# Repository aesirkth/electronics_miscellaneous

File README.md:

# electronics_miscellaneous
Various smaller electronics projects

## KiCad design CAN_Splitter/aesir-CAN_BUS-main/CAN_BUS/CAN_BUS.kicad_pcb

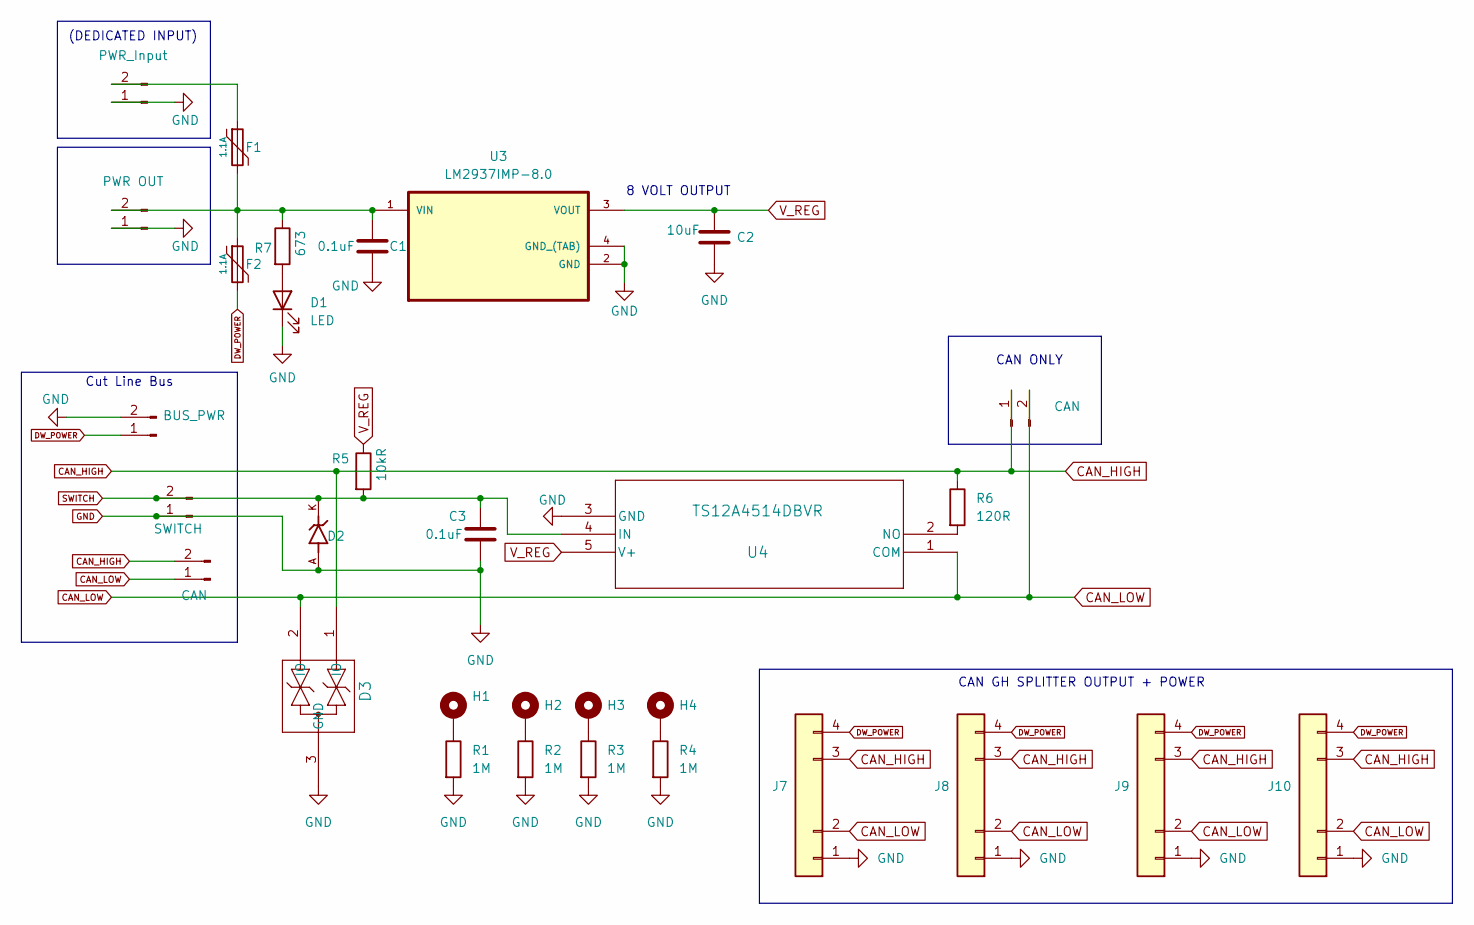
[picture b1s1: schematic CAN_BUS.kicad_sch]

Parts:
C1, C3: 0.1uF; C_0805_2012Metric_Pad1.18x1.45mm_HandSolder
C2: 10uF; C_0805_2012Metric_Pad1.18x1.45mm_HandSolder
D1: LED; LED_1206_3216Metric_Pad1.42x1.75mm_HandSolder
D2: UCLAMP1071P.TNT; DIO_UCLAMP1071P.TNT; PARTREV 8.1
D3: ESD2CAN36DBZRQ1; SOT-23-3_DBZ_TEX
F1, F2: 1.1A; Fuse_1812_4532Metric_Pad1.30x3.40mm_HandSolder
H1, H2, H3, H4: MountingHole_Pad; MountingHole_3.2mm_M3_Pad_Via
J1: PWR_Input; JST_VH_B2P-VH-FB-B_1x02_P3.96mm_Vertical
J2: PWR OUT; JST_VH_B2P-VH-FB-B_1x02_P3.96mm_Vertical
J3: BUS_PWR; JST_VH_B2P-VH-FB-B_1x02_P3.96mm_Vertical
J4: SWITCH; JST_XH_B2B-XH-A_1x02_P2.50mm_Vertical
J5, J6: CAN; JST_XH_B2B-XH-A_1x02_P2.50mm_Vertical
J7, J8, J9, J10: CAN+PWR; JST_GH_BM04B-GHS-TBT_1x04-1MP_P1.25mm_Vertical
R1, R2, R3, R4: 1M; R_0805_2012Metric_Pad1.20x1.40mm_HandSolder
R5: 10kR; R_0805_2012Metric_Pad1.20x1.40mm_HandSolder
R6: 120R; R_0805_2012Metric_Pad1.20x1.40mm_HandSolder
R7: 673; R_0805_2012Metric_Pad1.20x1.40mm_HandSolder
U3: LM2937IMP-8.0; SOT230P700X180-4N
U4: TS12A4514DBVR; DBV5

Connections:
CAN_HIGH: D3.1 (IO), J5.2, J6.1, J7.3, J8.3, J9.3, J10.3, R6.1
CAN_LOW: D3.2 (IO), J5.1, J6.2, J7.2, J8.2, J9.2, J10.2, U4.1 (COM)
DW_POWER: F2.2, J3.1, J7.4, J8.4, J9.4, J10.4
GND: C1.1, C2.1, C3.1, D1.1 (K), D2.A, D3.3 (GND), J1.1, J2.1, J3.2, J4.1, J7.1, J8.1, J9.1, J10.1, R1.2, R2.2, R3.2, R4.2, U3.2 (GND), U3.4 (GND_(TAB)), U4.3 (GND)
unnamed: D1.2 (A), R7.2
unnamed: H1.1, R1.1
unnamed: H2.1, R2.1
unnamed: H3.1, R3.1
unnamed: H4.1, R4.1
unnamed: F1.1, J1.2
unnamed: C1.2, F1.2, F2.1, J2.2, R7.1, U3.1 (VIN)
unnamed: R6.2, U4.2 (NO)
SWITCH: C3.2, D2.K, J4.2, R5.2, U4.4 (IN)
V_REG: C2.2, R5.1, U3.3 (VOUT), U4.5 (V+)

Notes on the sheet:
CAN GH SPLITTER OUTPUT + POWER
8 VOLT OUTPUT
Cut Line Bus
(DEDICATED INPUT)
CAN ONLY

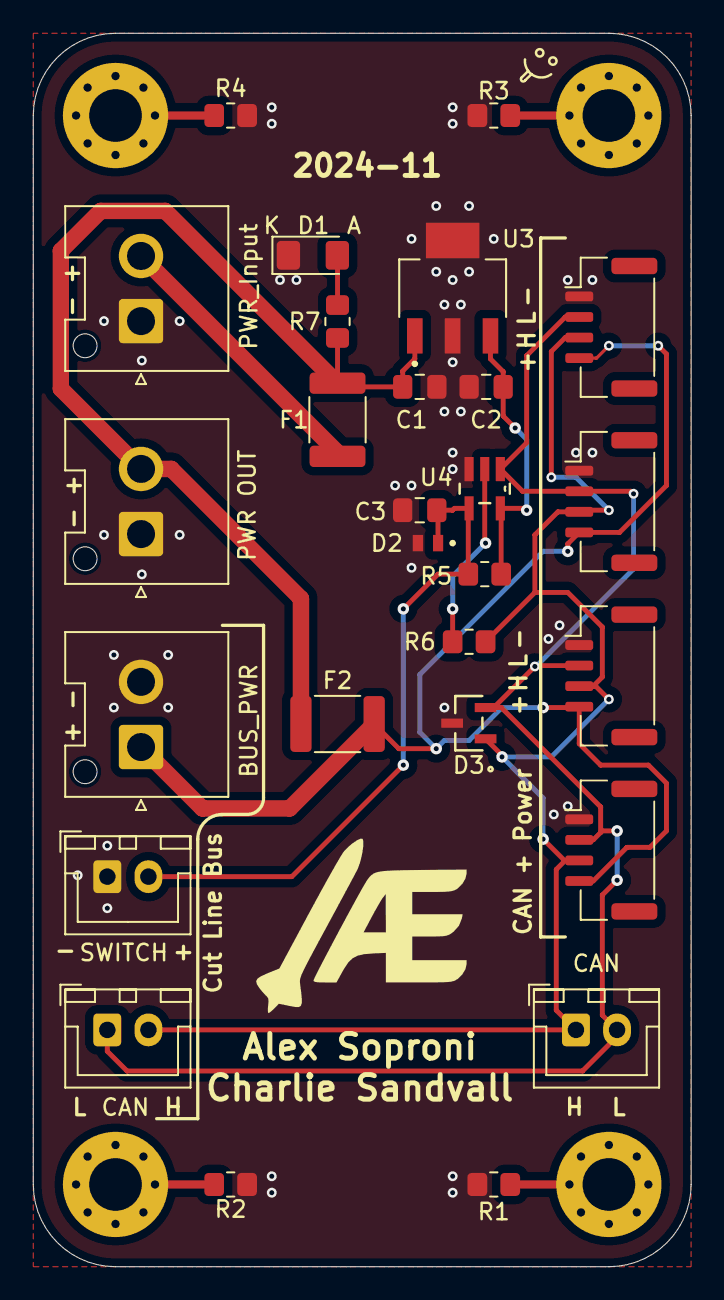
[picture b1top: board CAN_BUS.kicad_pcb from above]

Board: 2 copper layers, 40.0 x 75.0 mm, 31 parts (0 on the bottom side), 14 nets.

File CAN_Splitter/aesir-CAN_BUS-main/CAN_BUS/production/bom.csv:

Designator,Footprint,Quantity,Value,LCSC Part #
"C1, C3",0805,2,0.1uF,
C2,0805,1,10uF,
D1,1206,1,LED,
D2,DIO_UCLAMP1071P.TNT,1,UCLAMP1071P.TNT,
D3,SOT-23-3_DBZ_TEX,1,ESD2CAN36DBZRQ1,
"F1, F2",1812,2,1.1A,
J1,JST_VH_B2P-VH-FB-B_1x02_P3.96mm_Vertical,1,PWR_Input,
"J10, J7, J8, J9",JST_GH_BM04B-GHS-TBT_1x04-1MP_P1.25mm_Vertical,4,CAN+PWR,
J2,JST_VH_B2P-VH-FB-B_1x02_P3.96mm_Vertical,1,PWR OUT,
J3,JST_VH_B2P-VH-FB-B_1x02_P3.96mm_Vertical,1,BUS_PWR,
J4,JST_XH_B2B-XH-A_1x02_P2.50mm_Vertical,1,SWITCH,
"J5, J6",JST_XH_B2B-XH-A_1x02_P2.50mm_Vertical,2,CAN,
"R1, R2, R3, R4",0805,4,1M,
R5,0805,1,10kR,
R6,0805,1,120R,
R7,0805,1,402R,
U3,SOT230P700X180-4N,1,LM2937IMP-8.0,
U4,DBV5,1,TS12A4514DBVR,

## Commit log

2024-11-14 Create can_distributor
2024-11-14 Create Read_me
